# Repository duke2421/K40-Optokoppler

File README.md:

# K40-Optokoppler
Platine mit Optokoppler um das K40-Netzteil mit PWM anzusteuern

Erstellt mit KiCad

Mit dieser Platine kann der L Anschluss vom K40 Netzteil (MYJG 40W) mit PWM angesteuert werden. 

Mein K40 wird mit dem MPCNC-Nano-Estlcam-Shield angesteuert. An diese Optokoppler-Platine kann der Spindelausgang, bzw. die PWM vom Arduino Nano angeschlossen werden, der Stecker vom K40 Netzteil wird dann einfach an diese Platine gesteckt, keine weiteren Änderungen an der Verkabelung vom Netzteil notwendig. Die 24V für die Schrittmotoren und die Steuerung selber wird durch ein zusätzliches Netzteil zur Verfügung gestellt, wobei auch die 24V aus dem Lasernetzteil gehen sollten, das habe ich aber nicht getestet.

Im Ordner "Halter" ist noch ein kleines STL, bzw. FreeCAD-File für einen Abstandhalter. Damit kann die Platine ans Blech des K40 isoliert angeschraubt werden.

Verwendung auf eigene Gefahr, wenn nach Einbau dieser Platine euer K40 nicht mehr funktioniert, seid Ihr selbst schuld, nicht ich ;)

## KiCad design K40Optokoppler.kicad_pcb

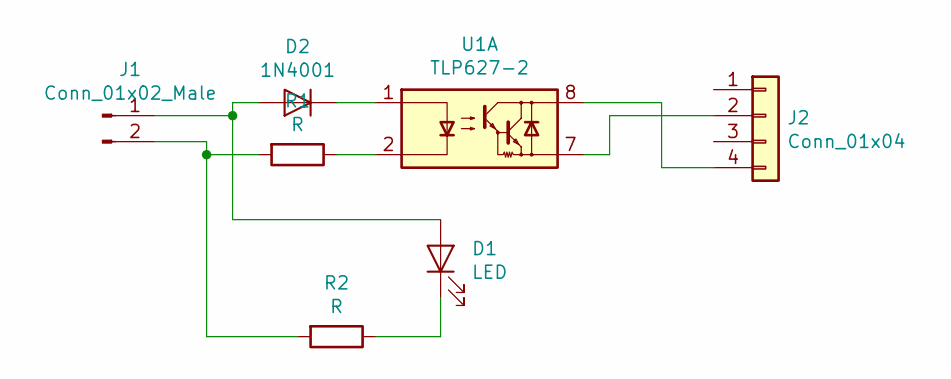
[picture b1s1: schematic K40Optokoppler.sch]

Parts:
D1: LED; LED_D5.0mm
D2: 1N4001; D_DO-41_SOD81_P10.16mm_Horizontal
J1: Conn_01x02_Male; PinHeader_1x02_P2.54mm_Horizontal
J2: Conn_01x04; JST-4.2mm_1x4
R1, R2: R; R_Axial_DIN0207_L6.3mm_D2.5mm_P7.62mm_Horizontal
U1: TLP627-2; DIP-8_W7.62mm

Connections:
unnamed: D1.1 (K), R2.1
unnamed: D1.2 (A), D2.2 (A), J1.1
unnamed: D2.1 (K), U1.1
unnamed: J1.2, R1.2, R2.2
unnamed: J2.2, U1.7
unnamed: J2.4, U1.8
unnamed: R1.1, U1.2

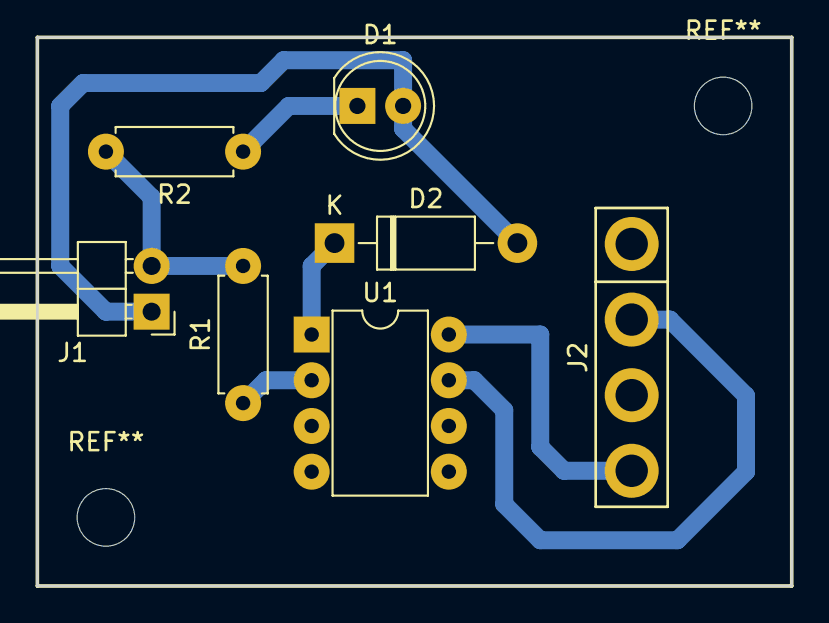
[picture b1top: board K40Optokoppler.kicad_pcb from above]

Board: 2 copper layers, 41.9 x 30.5 mm, 7 parts (0 on the bottom side), 7 nets.

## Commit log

2020-07-02 Erstes Release
2020-07-02 Step-Datei
    Step-Datei der Platine hinzugefügt
